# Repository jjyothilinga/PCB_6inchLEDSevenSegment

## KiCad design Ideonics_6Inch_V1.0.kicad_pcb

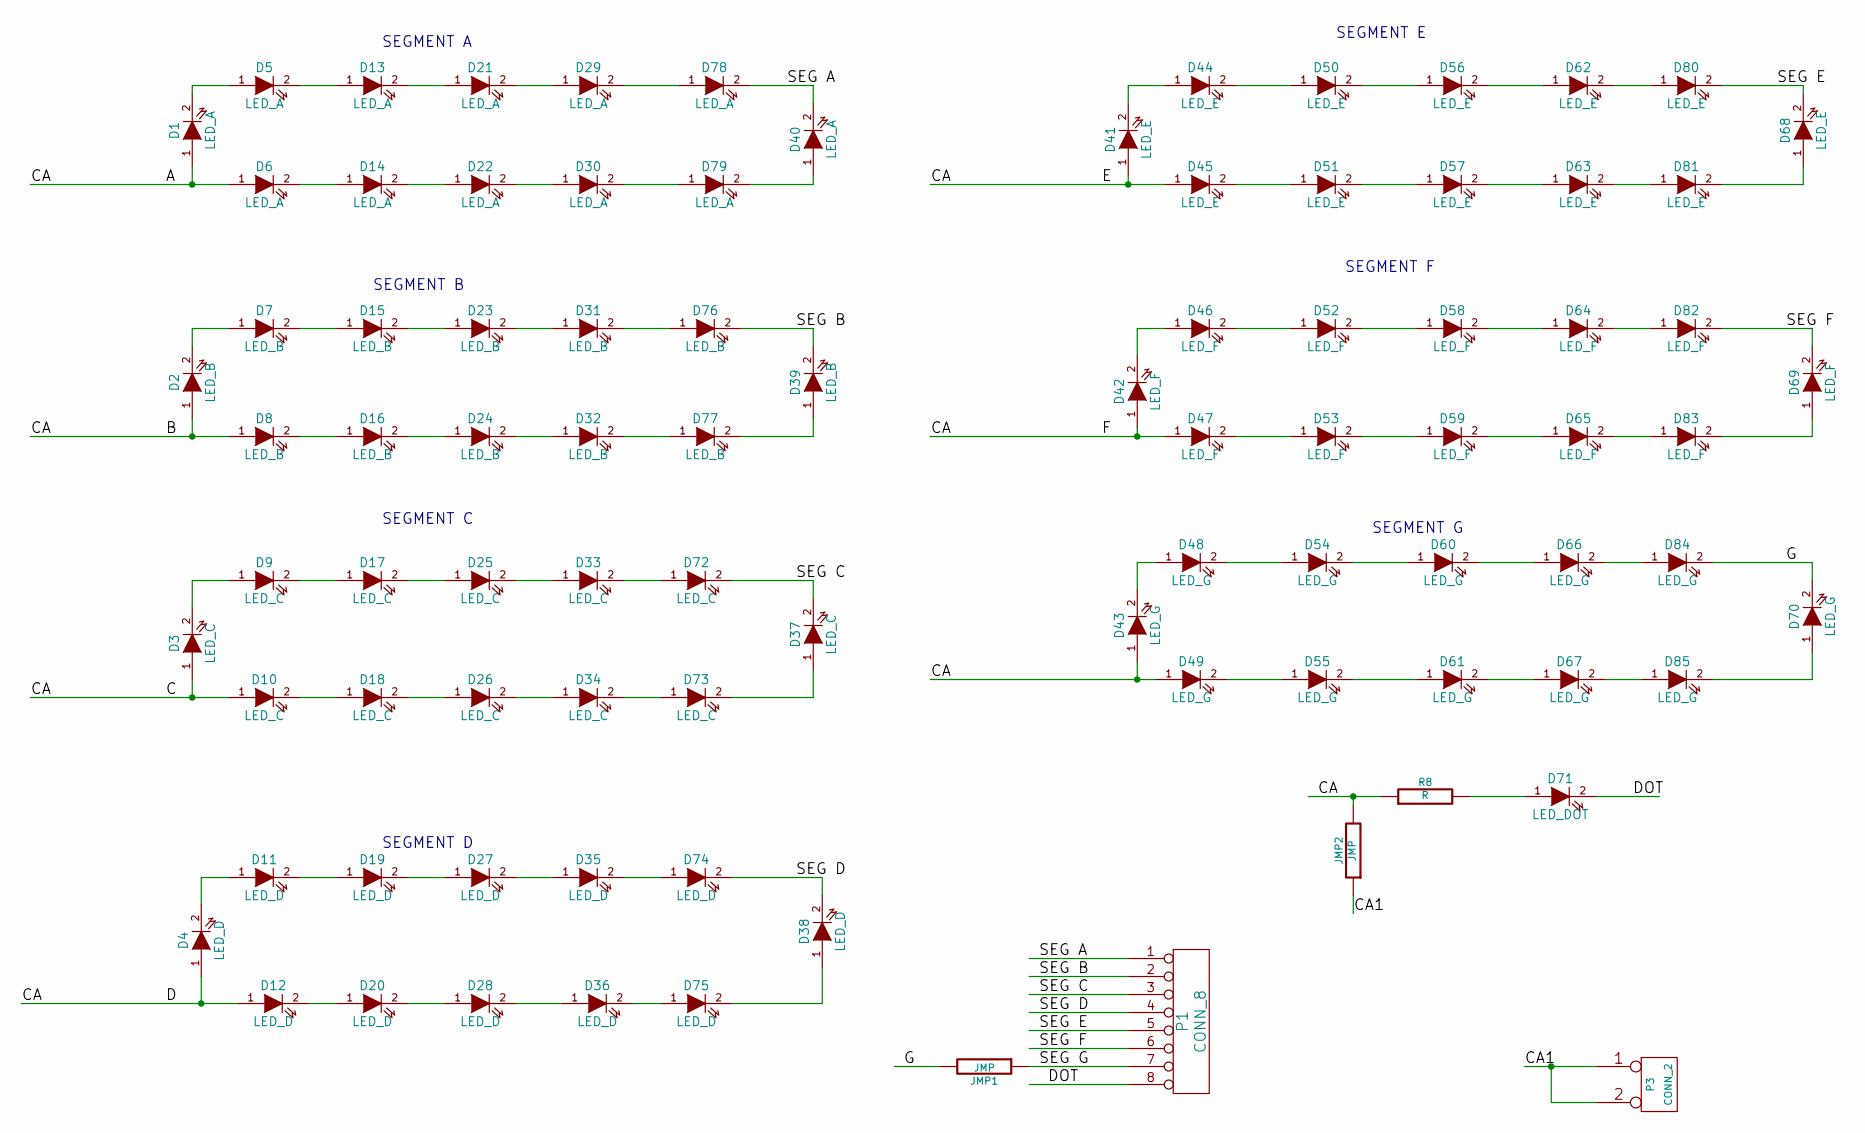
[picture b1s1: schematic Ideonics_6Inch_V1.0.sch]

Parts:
D1, D5, D6, D13, D14, D21, D22, D29, D30, D40, D78, D79: LED_A
D2, D7, D8, D15, D16, D23, D24, D31, D32, D39, D76, D77: LED_B
D3, D9, D10, D17, D18, D25, D26, D33, D34, D37, D72, D73: LED_C
D4, D11, D12, D19, D20, D27, D28, D35, D36, D38, D74, D75: LED_D
D41, D44, D45, D50, D51, D56, D57, D62, D63, D68, D80, D81: LED_E
D42, D46, D47, D52, D53, D58, D59, D64, D65, D69, D82, D83: LED_F
D43, D48, D49, D54, D55, D60, D61, D66, D67, D70, D84, D85: LED_G
D71: LED_DOT
JMP1, JMP2: JMP
P1: CONN_8
P3: CONN_2
R8: R

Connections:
/A: D1.1 (A), D2.1 (A), D3.1 (A), D4.1 (A), D6.1 (A), D8.1 (A), D10.1 (A), D12.1 (A), D41.1 (A), D42.1 (A), D43.1 (A), D45.1 (A), D47.1 (A), D49.1 (A), JMP2.2, R8.1
/CA1: JMP2.1, P3.1, P3.2 (PM)
/DOT: D71.2 (K), P1.8
/G: D70.2 (K), D84.2 (K), JMP1.2
/SEG A: D40.2 (K), D78.2 (K), P1.1
/SEG B: D39.2 (K), D76.2 (K), P1.2
/SEG C: D37.2 (K), D72.2 (K), P1.3
/SEG D: D38.2 (K), D74.2 (K), P1.4
/SEG E: D68.2 (K), D80.2 (K), P1.5
/SEG F: D69.2 (K), D82.2 (K), P1.6
/SEG G: JMP1.1, P1.7
unnamed: D34.2 (K), D73.1 (A)
unnamed: D19.2 (K), D27.1 (A)
unnamed: D27.2 (K), D35.1 (A)
unnamed: D35.2 (K), D74.1 (A)
unnamed: D36.2 (K), D75.1 (A)
unnamed: D28.2 (K), D36.1 (A)
unnamed: D20.2 (K), D28.1 (A)
unnamed: D12.2 (K), D20.1 (A)
unnamed: D26.2 (K), D34.1 (A)
unnamed: D4.2 (K), D11.1 (A)
unnamed: D33.2 (K), D72.1 (A)
unnamed: D25.2 (K), D33.1 (A)
unnamed: D17.2 (K), D25.1 (A)
unnamed: D18.2 (K), D26.1 (A)
unnamed: D10.2 (K), D18.1 (A)
unnamed: D9.2 (K), D17.1 (A)
unnamed: D3.2 (K), D9.1 (A)
unnamed: D50.2 (K), D56.1 (A)
unnamed: D53.2 (K), D59.1 (A)
unnamed: D52.2 (K), D58.1 (A)
unnamed: D58.2 (K), D64.1 (A)
unnamed: D59.2 (K), D65.1 (A)
unnamed: D65.2 (K), D83.1 (A)
unnamed: D64.2 (K), D82.1 (A)
unnamed: D62.2 (K), D80.1 (A)
unnamed: D57.2 (K), D63.1 (A)
unnamed: D56.2 (K), D62.1 (A)
unnamed: D51.2 (K), D57.1 (A)
unnamed: D45.2 (K), D51.1 (A)
unnamed: D44.2 (K), D50.1 (A)
unnamed: D41.2 (K), D44.1 (A)
unnamed: D11.2 (K), D19.1 (A)
unnamed: D1.2 (K), D5.1 (A)
unnamed: D31.2 (K), D76.1 (A)
unnamed: D32.2 (K), D77.1 (A)
unnamed: D30.2 (K), D79.1 (A)
unnamed: D29.2 (K), D78.1 (A)
unnamed: D66.2 (K), D84.1 (A)
unnamed: D2.2 (K), D7.1 (A)
unnamed: D8.2 (K), D16.1 (A)
unnamed: D16.2 (K), D24.1 (A)
unnamed: D24.2 (K), D32.1 (A)
unnamed: D23.2 (K), D31.1 (A)
unnamed: D15.2 (K), D23.1 (A)
unnamed: D7.2 (K), D15.1 (A)
unnamed: D47.2 (K), D53.1 (A)
unnamed: D21.2 (K), D29.1 (A)
unnamed: D22.2 (K), D30.1 (A)
unnamed: D14.2 (K), D22.1 (A)
unnamed: D13.2 (K), D21.1 (A)
unnamed: D5.2 (K), D13.1 (A)
unnamed: D6.2 (K), D14.1 (A)
unnamed: D39.1 (A), D77.2 (K)
unnamed: D38.1 (A), D75.2 (K)
unnamed: D37.1 (A), D73.2 (K)
unnamed: D40.1 (A), D79.2 (K)
unnamed: D70.1 (A), D85.2 (K)
unnamed: D69.1 (A), D83.2 (K)
unnamed: D68.1 (A), D81.2 (K)
unnamed: D49.2 (K), D55.1 (A)
unnamed: D54.2 (K), D60.1 (A)
unnamed: D48.2 (K), D54.1 (A)
unnamed: D43.2 (K), D48.1 (A)
unnamed: D55.2 (K), D61.1 (A)
unnamed: D61.2 (K), D67.1 (A)
unnamed: D60.2 (K), D66.1 (A)
unnamed: D46.2 (K), D52.1 (A)
unnamed: D42.2 (K), D46.1 (A)
unnamed: D63.2 (K), D81.1 (A)
unnamed: D67.2 (K), D85.1 (A)
unnamed: D71.1 (A), R8.2

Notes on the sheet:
SEGMENT A
SEGMENT B
SEGMENT C
SEGMENT D
SEGMENT E
SEGMENT F
SEGMENT G

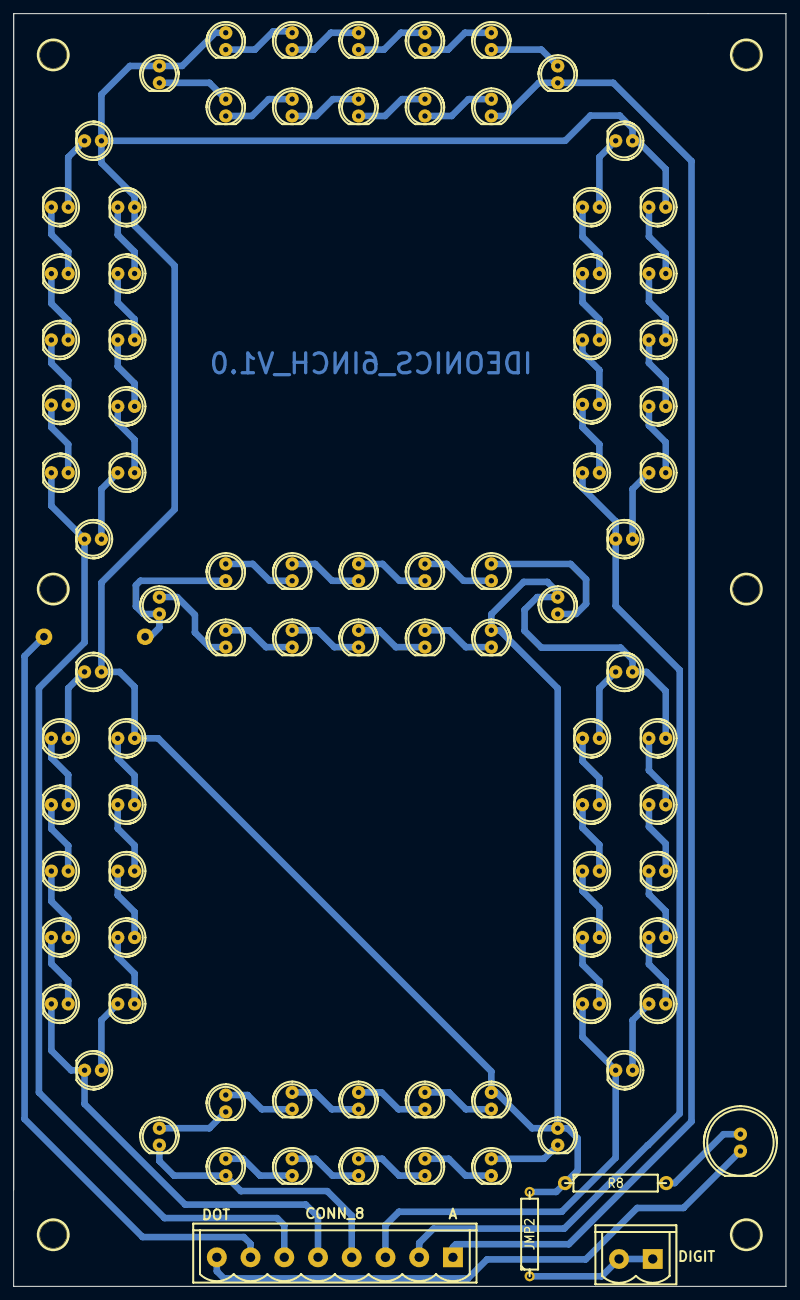
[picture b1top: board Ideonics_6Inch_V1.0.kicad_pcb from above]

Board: 2 copper layers, 116.3 x 191.7 mm, 96 parts (1 on the bottom side), 82 nets.

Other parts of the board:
1PIN, 1PIN#2, 1PIN#3, 1PIN#4, 1PIN#5, 1PIN#6: P***; 1pin

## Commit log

2016-02-05 :confetti_ball: Added .gitattributes & .gitignore files
2016-02-05 Completed
